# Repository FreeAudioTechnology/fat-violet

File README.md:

# violet
Open Source Microphone System with integrated ADC, digital phantom power, AES42, large diaphragm condenser capsule support

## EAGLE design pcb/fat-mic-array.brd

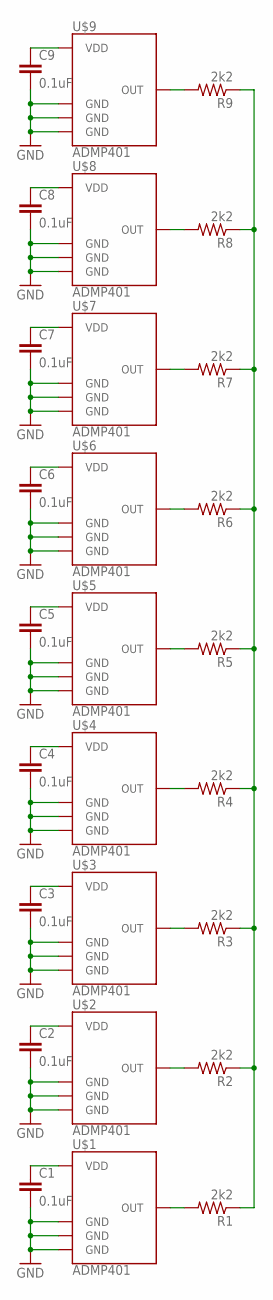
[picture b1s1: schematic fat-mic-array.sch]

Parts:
C1, C2, C3, C4, C5, C6, C7, C8, C9: 0.1uF; 0402-CAP
R1, R2, R3, R4, R5, R6, R7, R8, R9: 2k2; 0402-RES
U$1, U$2, U$3, U$4, U$5, U$6, U$7, U$8, U$9: ADMP401

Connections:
GND: C1.2, C2.2, C3.2, C4.2, C5.2, C6.2, C7.2, C8.2, C9.2, U$1.2 (GND), U$1.4 (GND), U$1.6 (GND), U$2.2 (GND), U$2.4 (GND), U$2.6 (GND), U$3.2 (GND), U$3.4 (GND), U$3.6 (GND), U$4.2 (GND), U$4.4 (GND), U$4.6 (GND), U$5.2 (GND), U$5.4 (GND), U$5.6 (GND), U$6.2 (GND), U$6.4 (GND), U$6.6 (GND), U$7.2 (GND), U$7.4 (GND), U$7.6 (GND), U$8.2 (GND), U$8.4 (GND), U$8.6 (GND), U$9.2 (GND), U$9.4 (GND), U$9.6 (GND)
unnamed: R1.2, U$1.1 (OUT)
unnamed: C1.1, U$1.5 (VDD)
unnamed: R3.2, U$3.1 (OUT)
unnamed: R1.1, R2.1, R3.1, R4.1, R5.1, R6.1, R7.1, R8.1, R9.1
unnamed: R2.2, U$2.1 (OUT)
unnamed: C2.1, U$2.5 (VDD)
unnamed: C3.1, U$3.5 (VDD)
unnamed: R4.2, U$4.1 (OUT)
unnamed: C4.1, U$4.5 (VDD)
unnamed: R5.2, U$5.1 (OUT)
unnamed: C5.1, U$5.5 (VDD)
unnamed: R6.2, U$6.1 (OUT)
unnamed: C6.1, U$6.5 (VDD)
unnamed: R7.2, U$7.1 (OUT)
unnamed: C7.1, U$7.5 (VDD)
unnamed: R8.2, U$8.1 (OUT)
unnamed: C8.1, U$8.5 (VDD)
unnamed: R9.2, U$9.1 (OUT)
unnamed: C9.1, U$9.5 (VDD)

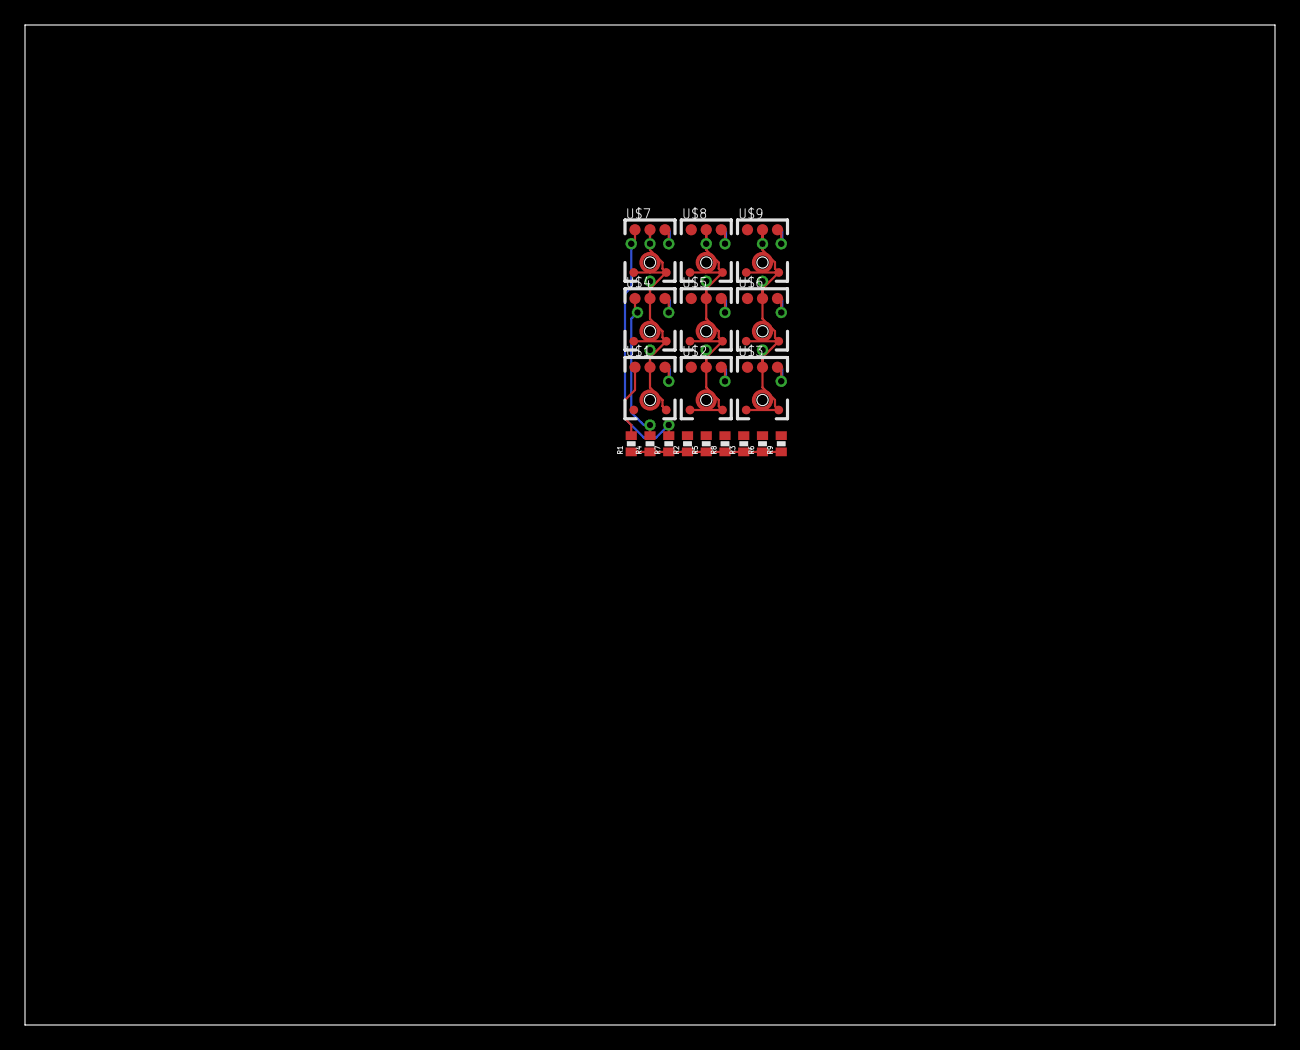
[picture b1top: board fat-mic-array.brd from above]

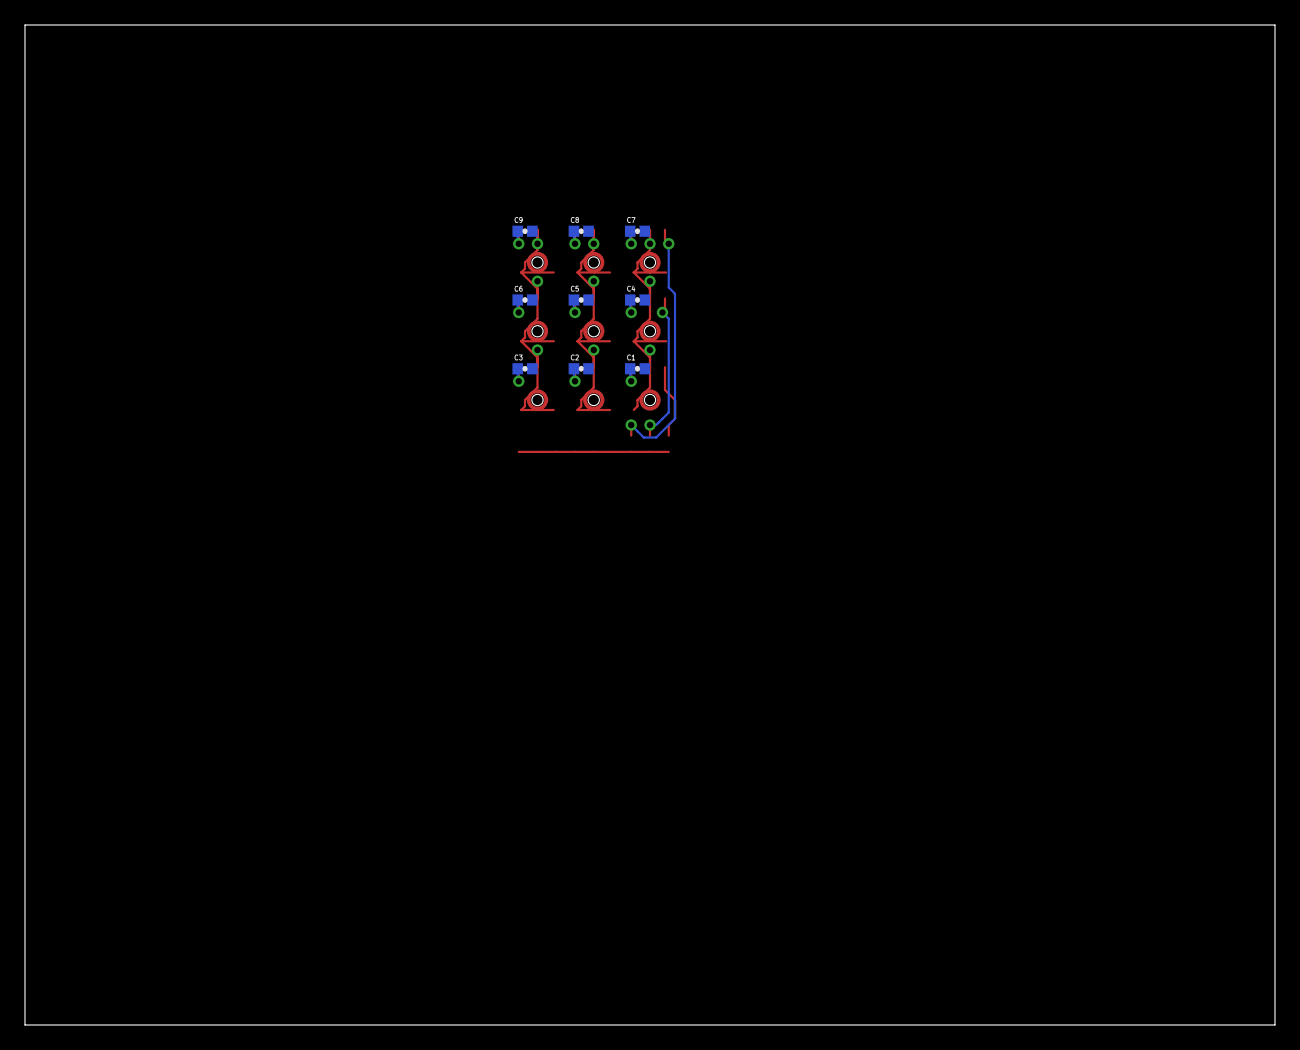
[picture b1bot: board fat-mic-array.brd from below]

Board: 2 copper layers, 100.0 x 80.0 mm, 27 parts (9 on the bottom side), 20 nets.

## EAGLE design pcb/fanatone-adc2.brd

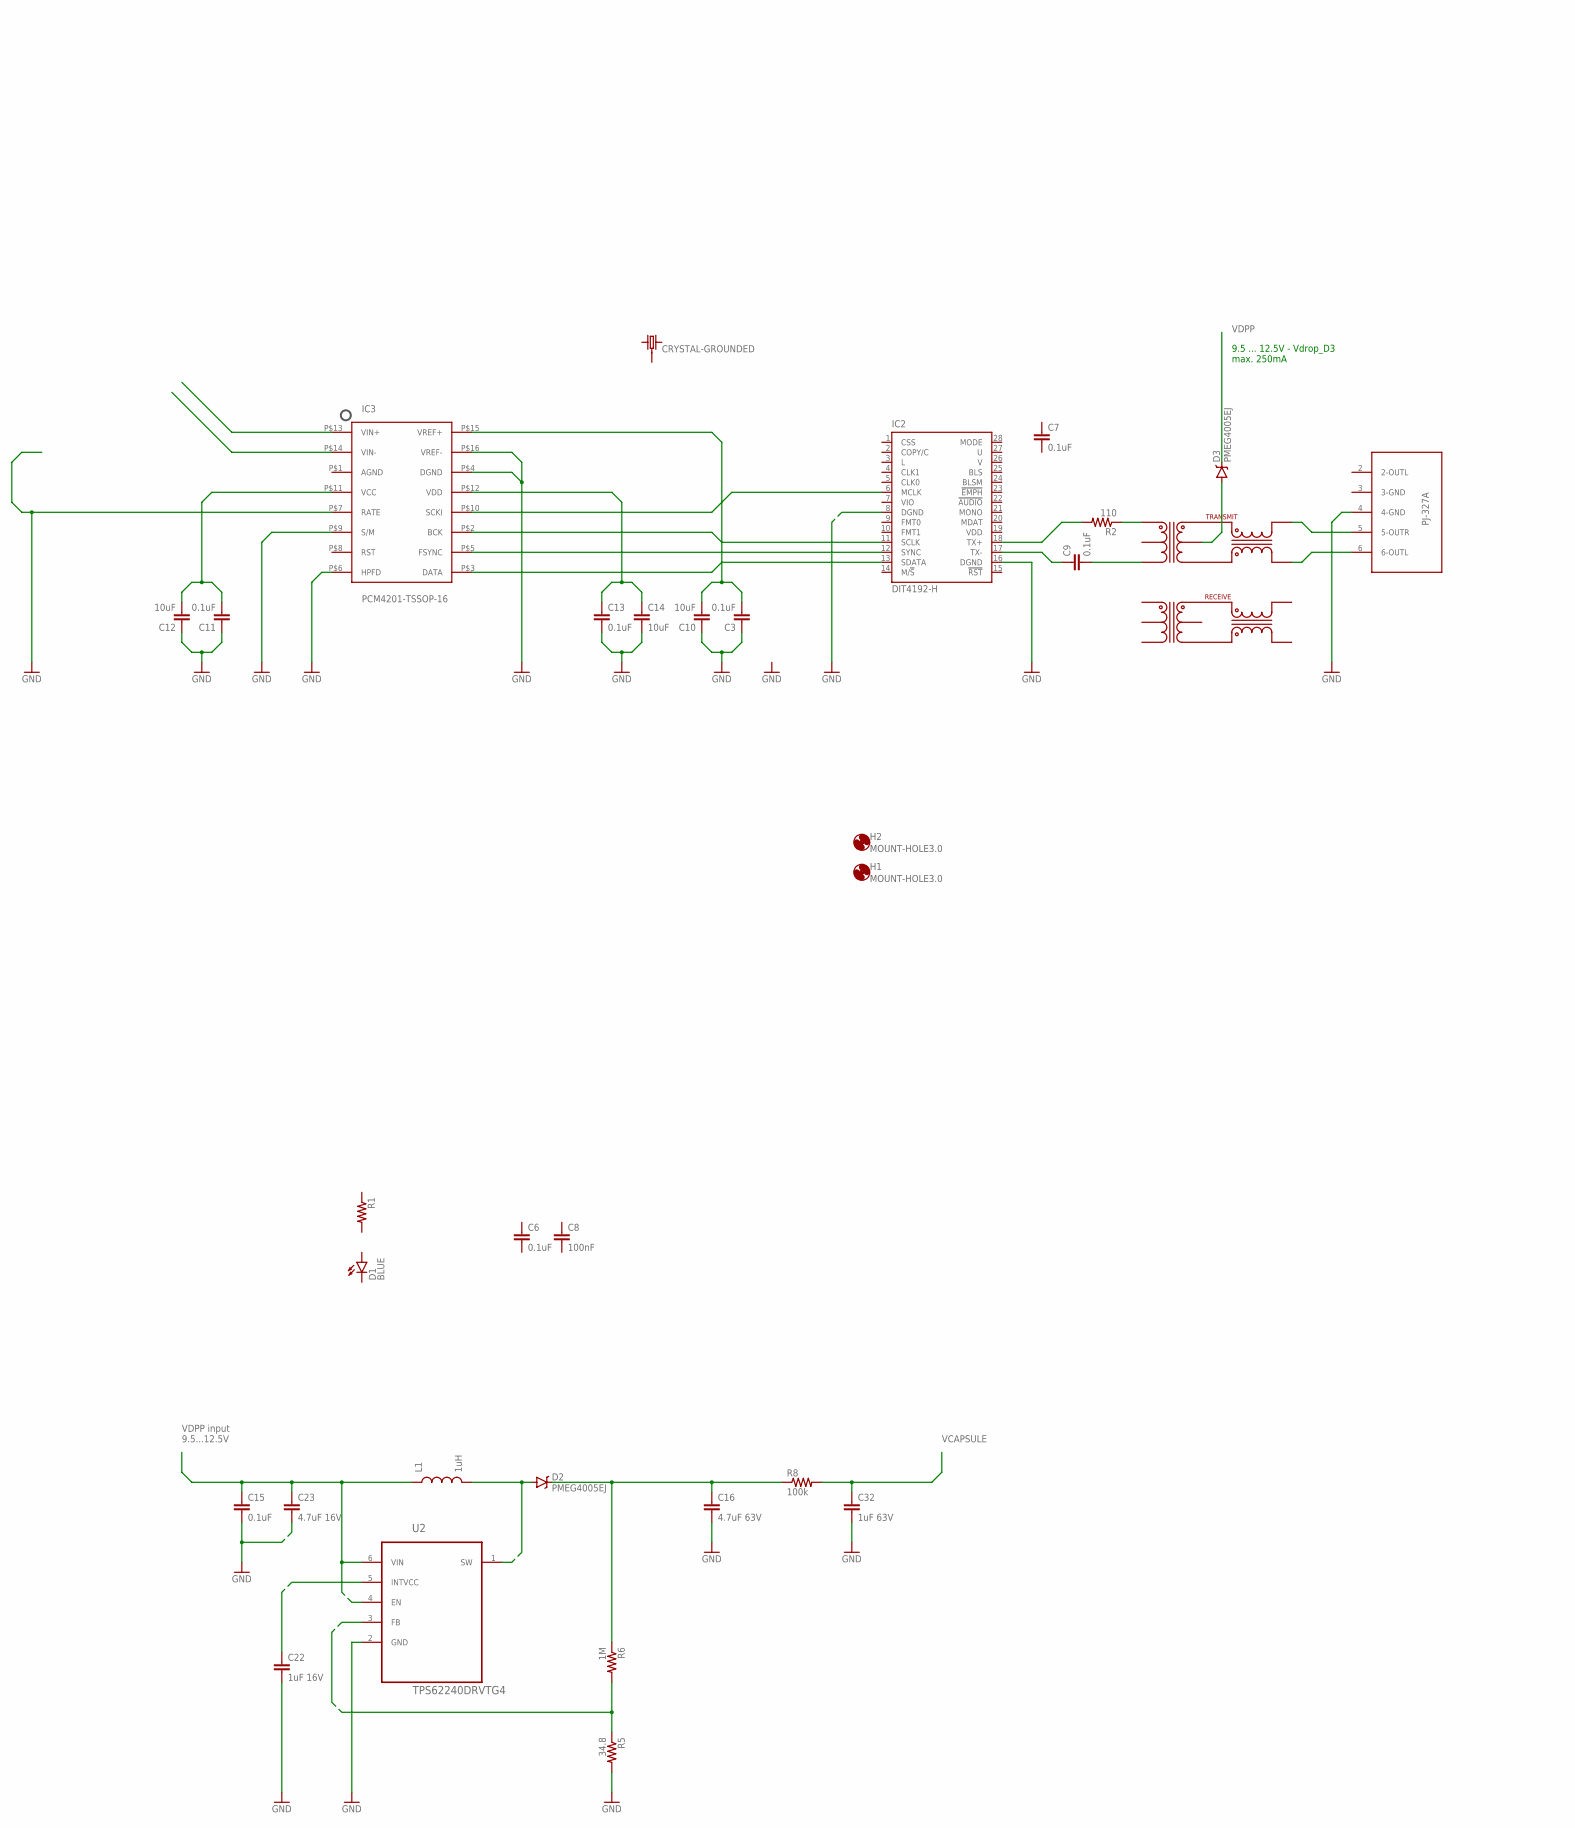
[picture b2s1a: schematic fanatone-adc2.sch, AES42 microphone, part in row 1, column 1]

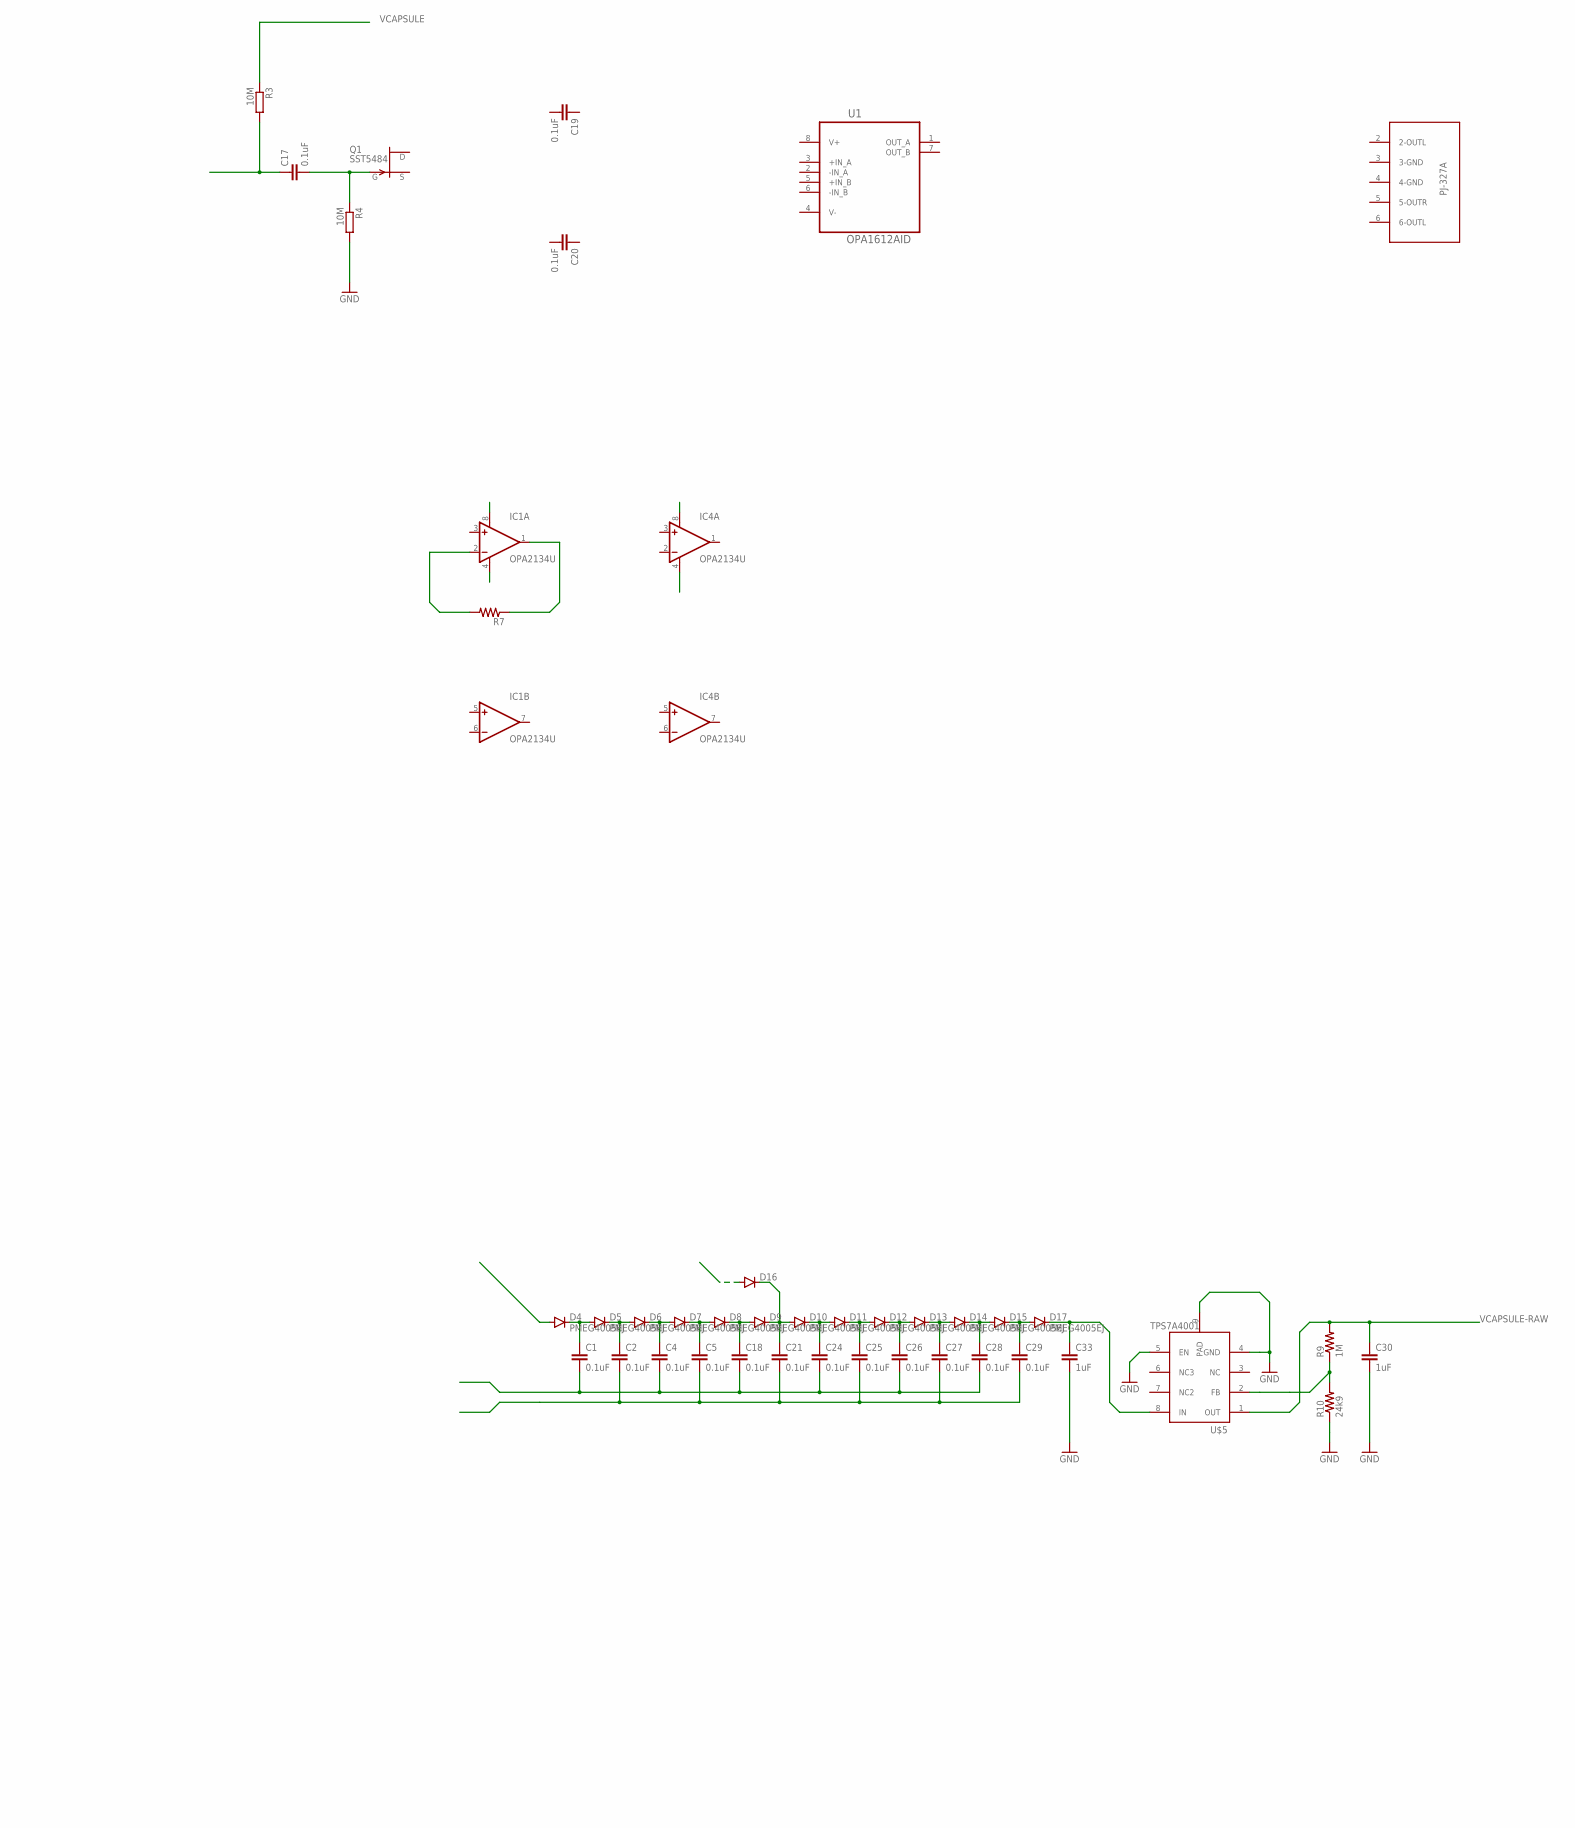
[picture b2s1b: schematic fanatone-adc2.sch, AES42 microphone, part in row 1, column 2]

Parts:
C1, C2, C3, C4, C5, C6, C7, C9, C11, C13, C15, C17, C18, C19, C20, C21, C24, C25, C26, C27, C28, C29: 0.1uF; 0402-CAP
C8: 100nF; 0402-CAP
C10, C12, C14: 10uF; 0805
C16: 4.7uF 63V; 0805
C22: 1uF 16V; 0805
C23: 4.7uF 16V; 0805
C30, C33: 1uF; 0805
C32: 1uF 63V; 0805
D1: BLUE; LED-0603
D2, D3: PMEG4005EJ; SOD-323
D4, D5, D6, D7, D8, D9, D10, D11, D12, D13, D14, D15, D17: PMEG4005EJ; SOD523
D16: DIODESOD523; SOD523
H1, H2: MOUNT-HOLE3.0; 3,0
IC1, IC4: OPA2134U; SO08
IC2: DIT4192-H; PW_R-PDSO-G28
IC3: PCM4201-TSSOP-16; TSSOP-16
L1: 1uH; 0805
Q1: SST5484; SOT23
R1, R7: RESISTOR0603-RES; 0603-RES
R2: 110; 0603-RES
R3, R4: 10M; R0805W
R5: 34.8; 0603-RES
R6, R9: 1M; 0603-RES
R8: 100k; 0603-RES
R10: 24k9; 0603-RES
U1: OPA1612AID; SOIC127P600X175-8N
U2: TPS62240DRVTG4; SON65P210X210X80-7N
U$1: CRYSTAL-GROUNDED; CRYSTAL-SMD-5X3
U$2, U$3: PJ-327A
U$4: H1102; H11XX
U$5: TPS7A4001; POWER-SOP8

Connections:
3V3: C13.1, C14.1, IC3.P$12 (VDD)
5V: C11.2, C12.2, IC3.P$11 (VCC)
GND: C3.1, C10.1, C11.1, C12.1, C13.2, C14.2, C15.2, C16.2, C22.2, C23.2, C30.2, C32.2, C33.2, IC2.8 (DGND), IC2.16 (DGND), IC3.P$4 (DGND), IC3.P$6 (HPFD), IC3.P$7 (RATE), IC3.P$9 (S/M), IC3.P$16 (VREF-), R4.2, R5.2, R10.1, U2.2 (GND), U$2.4 (4-GND), U$5.4 (GND), U$5.5 (EN), U$5.9 (PAD)
unnamed: C9.2, U$4.3
unnamed: R2.1, U$4.1
unnamed: C17.1, R3.2
unnamed: C17.2, Q1.3 (G), R4.1
unnamed: C3.2, C10.2, IC3.P$15 (VREF+)
unnamed: IC2.18 (TX+), R2.2
unnamed: R5.1, R6.2, U2.3 (FB)
unnamed: C22.1, U2.5 (INTVCC)
unnamed: C9.1, IC2.17 (TX-)
unnamed: D3.A, U$4.15
unnamed: D2.A, L1.2, U2.1 (SW)
unnamed: IC2.11 (SCLK), IC3.P$2 (BCK)
unnamed: C4.1, D6.C, D7.A
unnamed: IC2.12 (SYNC), IC3.P$5 (FSYNC)
unnamed: IC2.13 (SDATA), IC3.P$3 (DATA)
unnamed: U$2.6 (6-OUTL), U$4.14
unnamed: IC2.6 (MCLK), IC3.P$10 (SCKI)
unnamed: U$2.5 (5-OUTR), U$4.16
unnamed: IC1.1 (OUT), R7.1
unnamed: IC1.2 (-IN), R7.2
unnamed: C1.1, D4.C, D5.A
unnamed: C1.2, C4.2, C18.2, C24.2, C26.2, C28.2
unnamed: C2.1, D5.C, D6.A
unnamed: C2.2, C5.2, C21.2, C25.2, C27.2, C29.2
unnamed: C29.1, D15.C, D17.A
unnamed: C5.1, D7.C, D8.A
unnamed: R9.1, R10.2, U$5.2 (FB)
unnamed: C18.1, D8.C, D9.A
unnamed: C21.1, D9.C, D10.A, D16.C
unnamed: C24.1, D10.C, D11.A
unnamed: C25.1, D11.C, D12.A
unnamed: C26.1, D12.C, D13.A
unnamed: C27.1, D13.C, D14.A
unnamed: C28.1, D14.C, D15.A
unnamed: C33.1, D17.C, U$5.8 (IN)
V+: U1.8 (V+)
V-: U1.4 (V-)
VCAPSULE: C32.1, R3.1, R8.2
VCAPSULE-RAW: C16.1, C30.1, D2.C, R6.1, R8.1, R9.2, U$5.1 (OUT)
VDD: IC2.19 (VDD)
VDPP: C15.1, C23.1, D3.C, D16.A, L1.1, U2.4 (EN), U2.6 (VIN)
VIO: IC2.7 (VIO)

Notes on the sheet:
9.5 ... 12.5V - Vdrop_D3 max. 250mA
VDPP input 9.5...12.5V

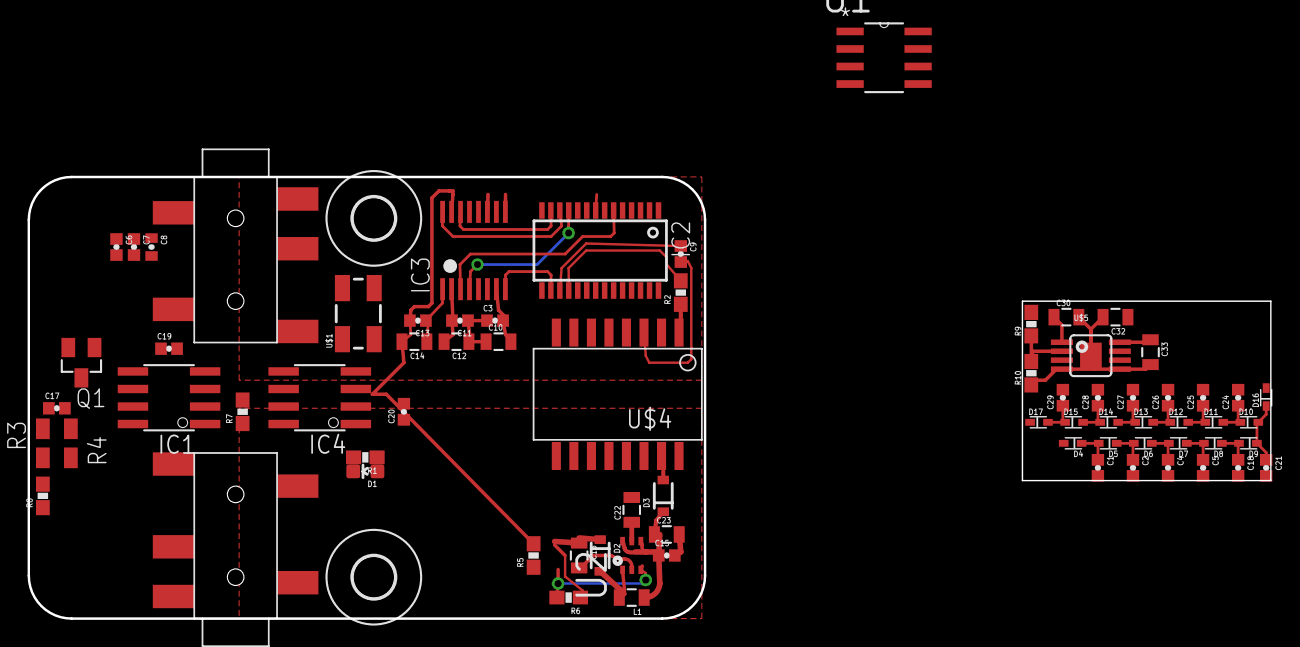
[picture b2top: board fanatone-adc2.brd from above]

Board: 2 copper layers, 90.0 x 32.0 mm, 74 parts (0 on the bottom side), 41 nets.

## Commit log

2016-02-16 add Eagle PCB src files WIP
2016-02-16 add datasheets, remove capacitor over R6 at booster
2016-02-16 step file exported from Fusion 360
2016-02-18 Rectangular FAT Capsule R design
2016-02-18 correct naming scheme, +animated exploded view
2016-02-19 start with OPA2134 at the initial gain stage
2016-02-22 evaluating DC charge pump/multiplier layouts
2016-02-23 Dickson charge pump layout, PCB wip, tidy up
2016-02-27 add concept for a MEMS Microphone array + step file sync + animation

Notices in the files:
parts and their libraries:
SparkFun-Passives: Licensing: Creative Commons ShareAlike 4.0 International - https://creativecommons.org/licenses/by-sa/4.0
